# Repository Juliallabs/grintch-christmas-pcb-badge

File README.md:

# grintch-christmas-pcb-badge
Um belíssimo adorno para arvore de natal no formato de uma figura icônica e muito natalina.

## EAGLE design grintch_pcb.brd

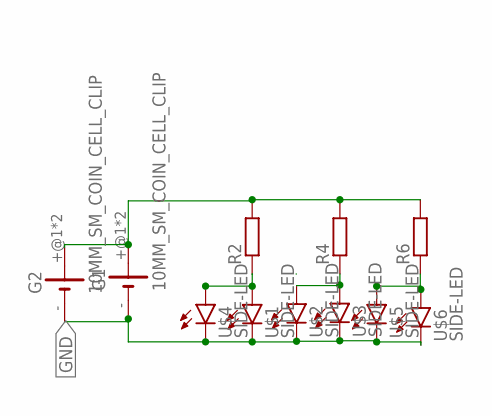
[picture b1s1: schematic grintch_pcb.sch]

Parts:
G1, G2: 10MM_SM_COIN_CELL_CLIP
R2, R4, R6: R-EU_R0805; R0805
U$1, U$2, U$3, U$4, U$5, U$6: SIDE-LED

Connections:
GND: G1.-, G2.-, U$1.P$2 (C), U$2.P$2 (C), U$3.P$2 (C), U$4.P$2 (C), U$5.P$2 (C), U$6.P$2 (C)
unnamed: G1.+@1 (+), G1.+@2 (+), G2.+@1 (+), G2.+@2 (+), R2.2, R4.2, R6.2
unnamed: R2.1, U$1.P$1 (A), U$4.P$1 (A)
unnamed: R4.1, U$2.P$1 (A), U$3.P$1 (A)
unnamed: R6.1, U$5.P$1 (A), U$6.P$1 (A)

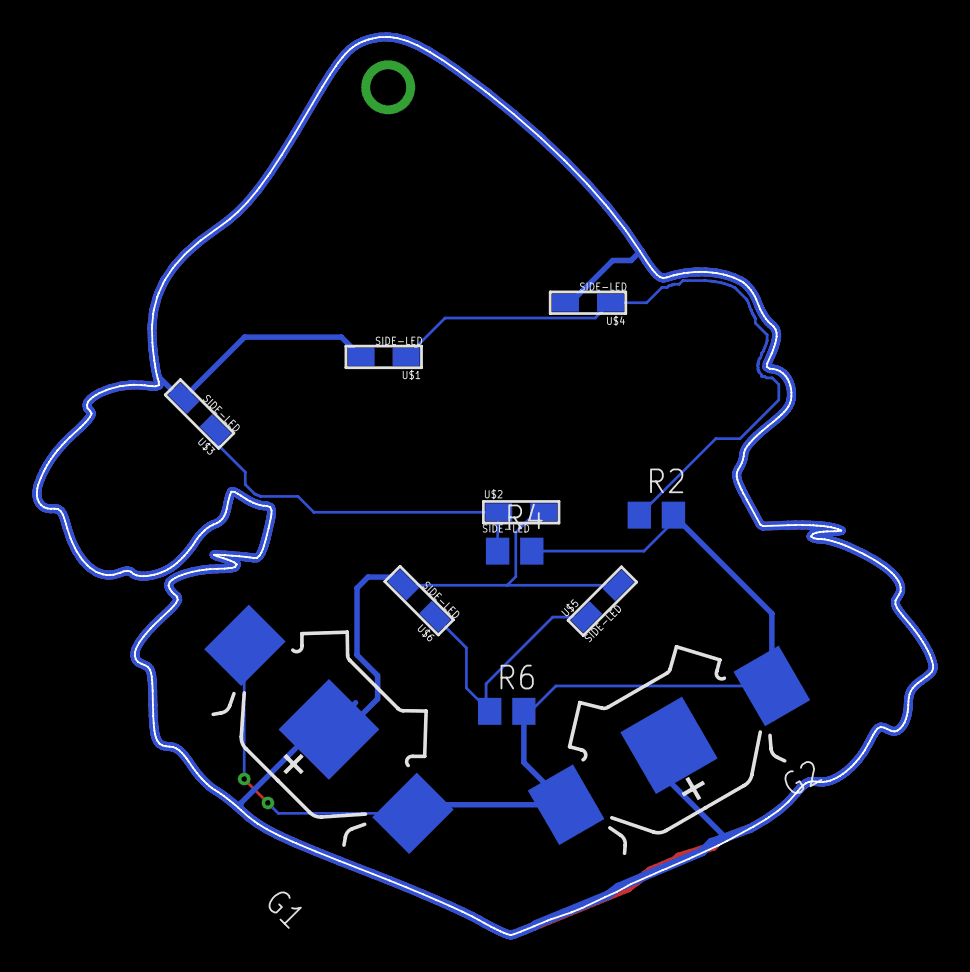
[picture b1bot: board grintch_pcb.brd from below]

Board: 2 copper layers, 49.8 x 49.9 mm, 11 parts (11 on the bottom side), 5 nets.

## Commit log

2021-03-22 init
2023-07-08 organizacao
2023-07-27 Revert "organizacao"
    This reverts commit 812361a77cd899cac17ceb17ba00c6320489ed3d.
